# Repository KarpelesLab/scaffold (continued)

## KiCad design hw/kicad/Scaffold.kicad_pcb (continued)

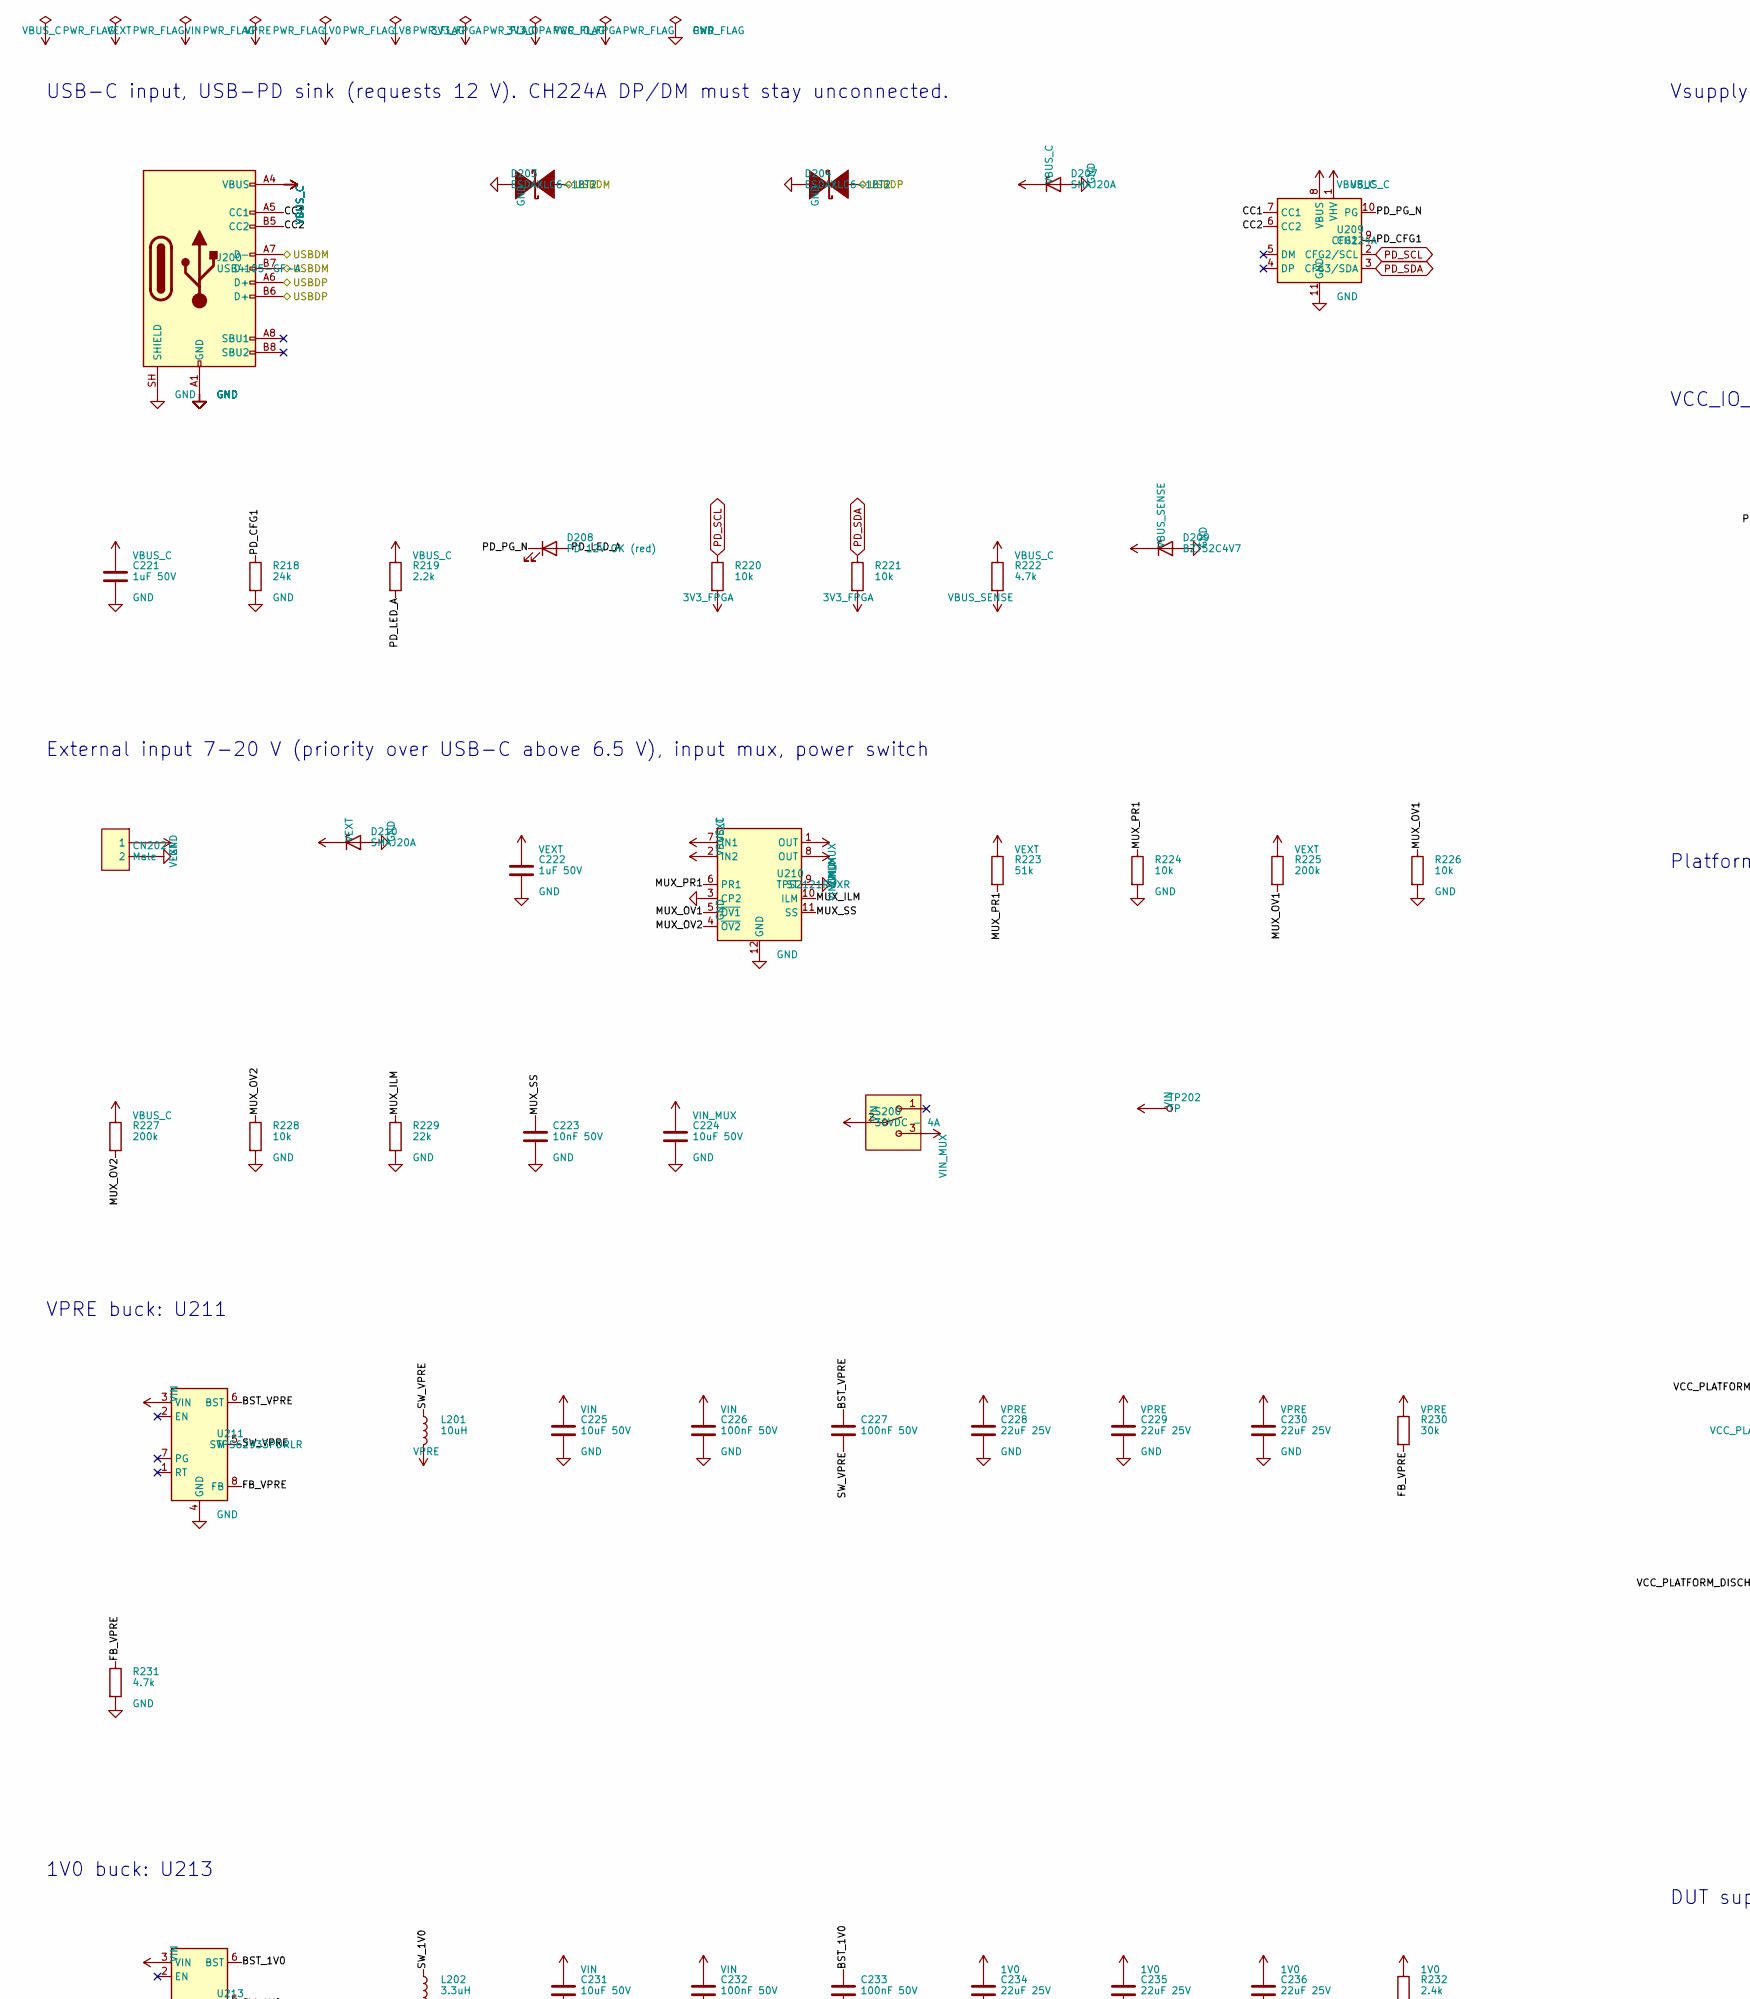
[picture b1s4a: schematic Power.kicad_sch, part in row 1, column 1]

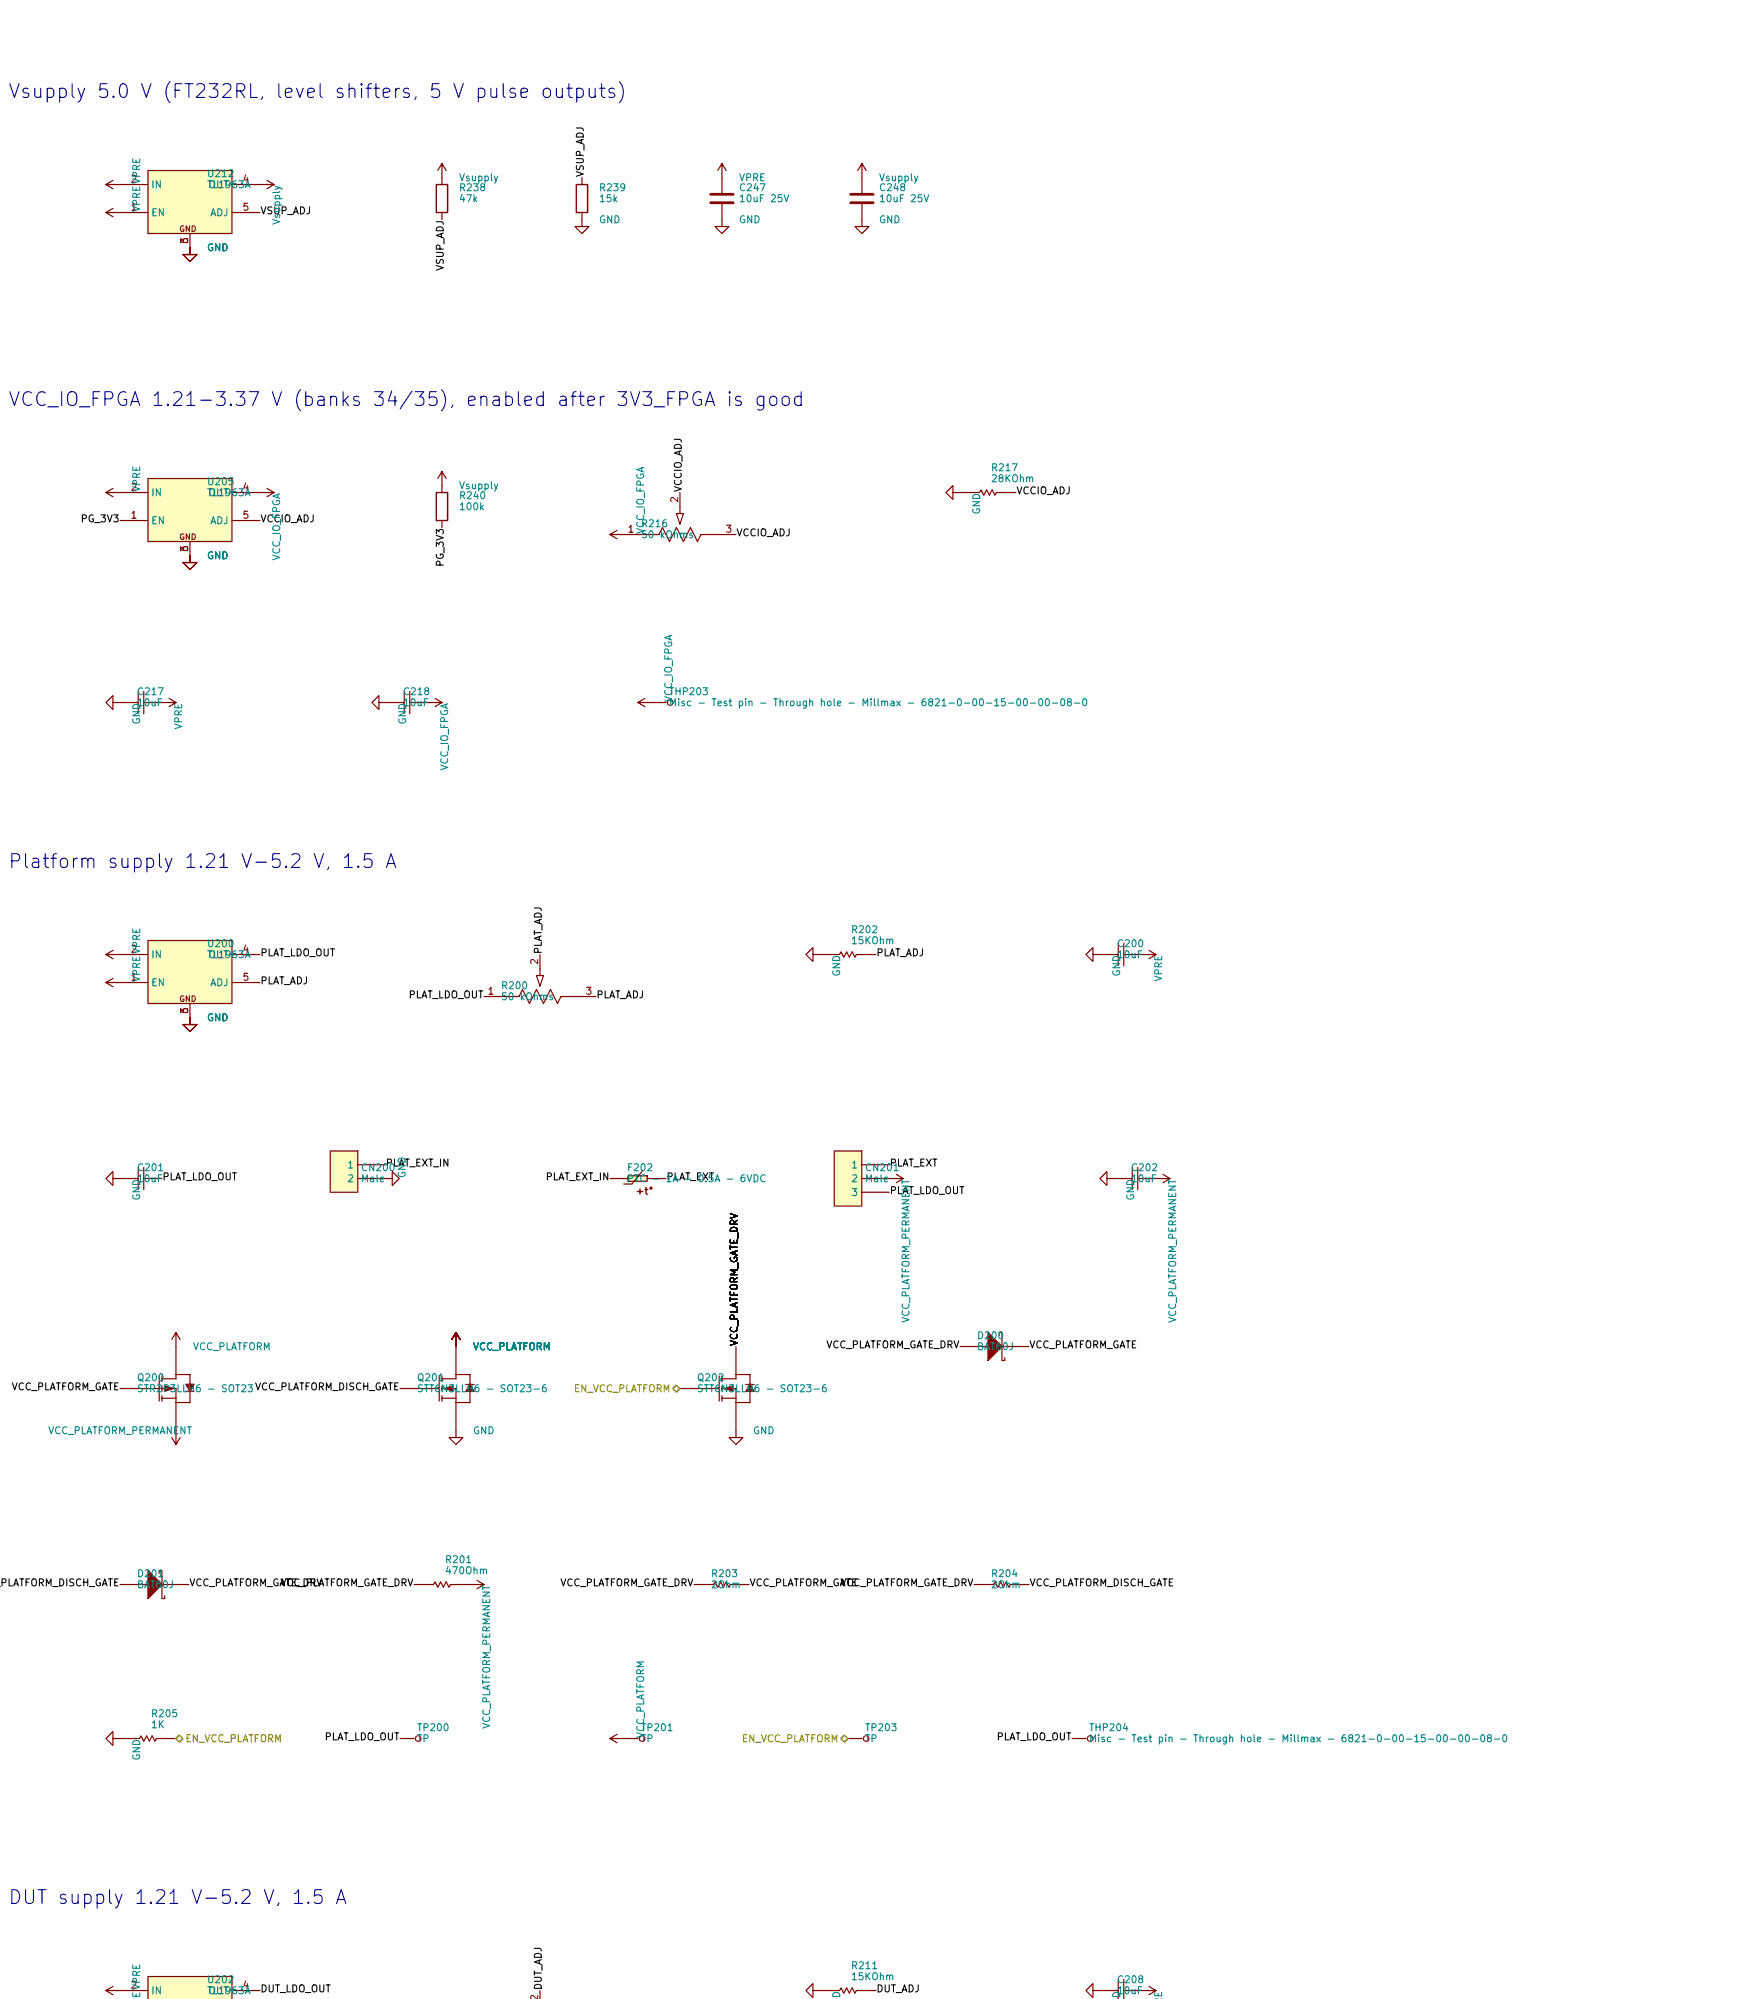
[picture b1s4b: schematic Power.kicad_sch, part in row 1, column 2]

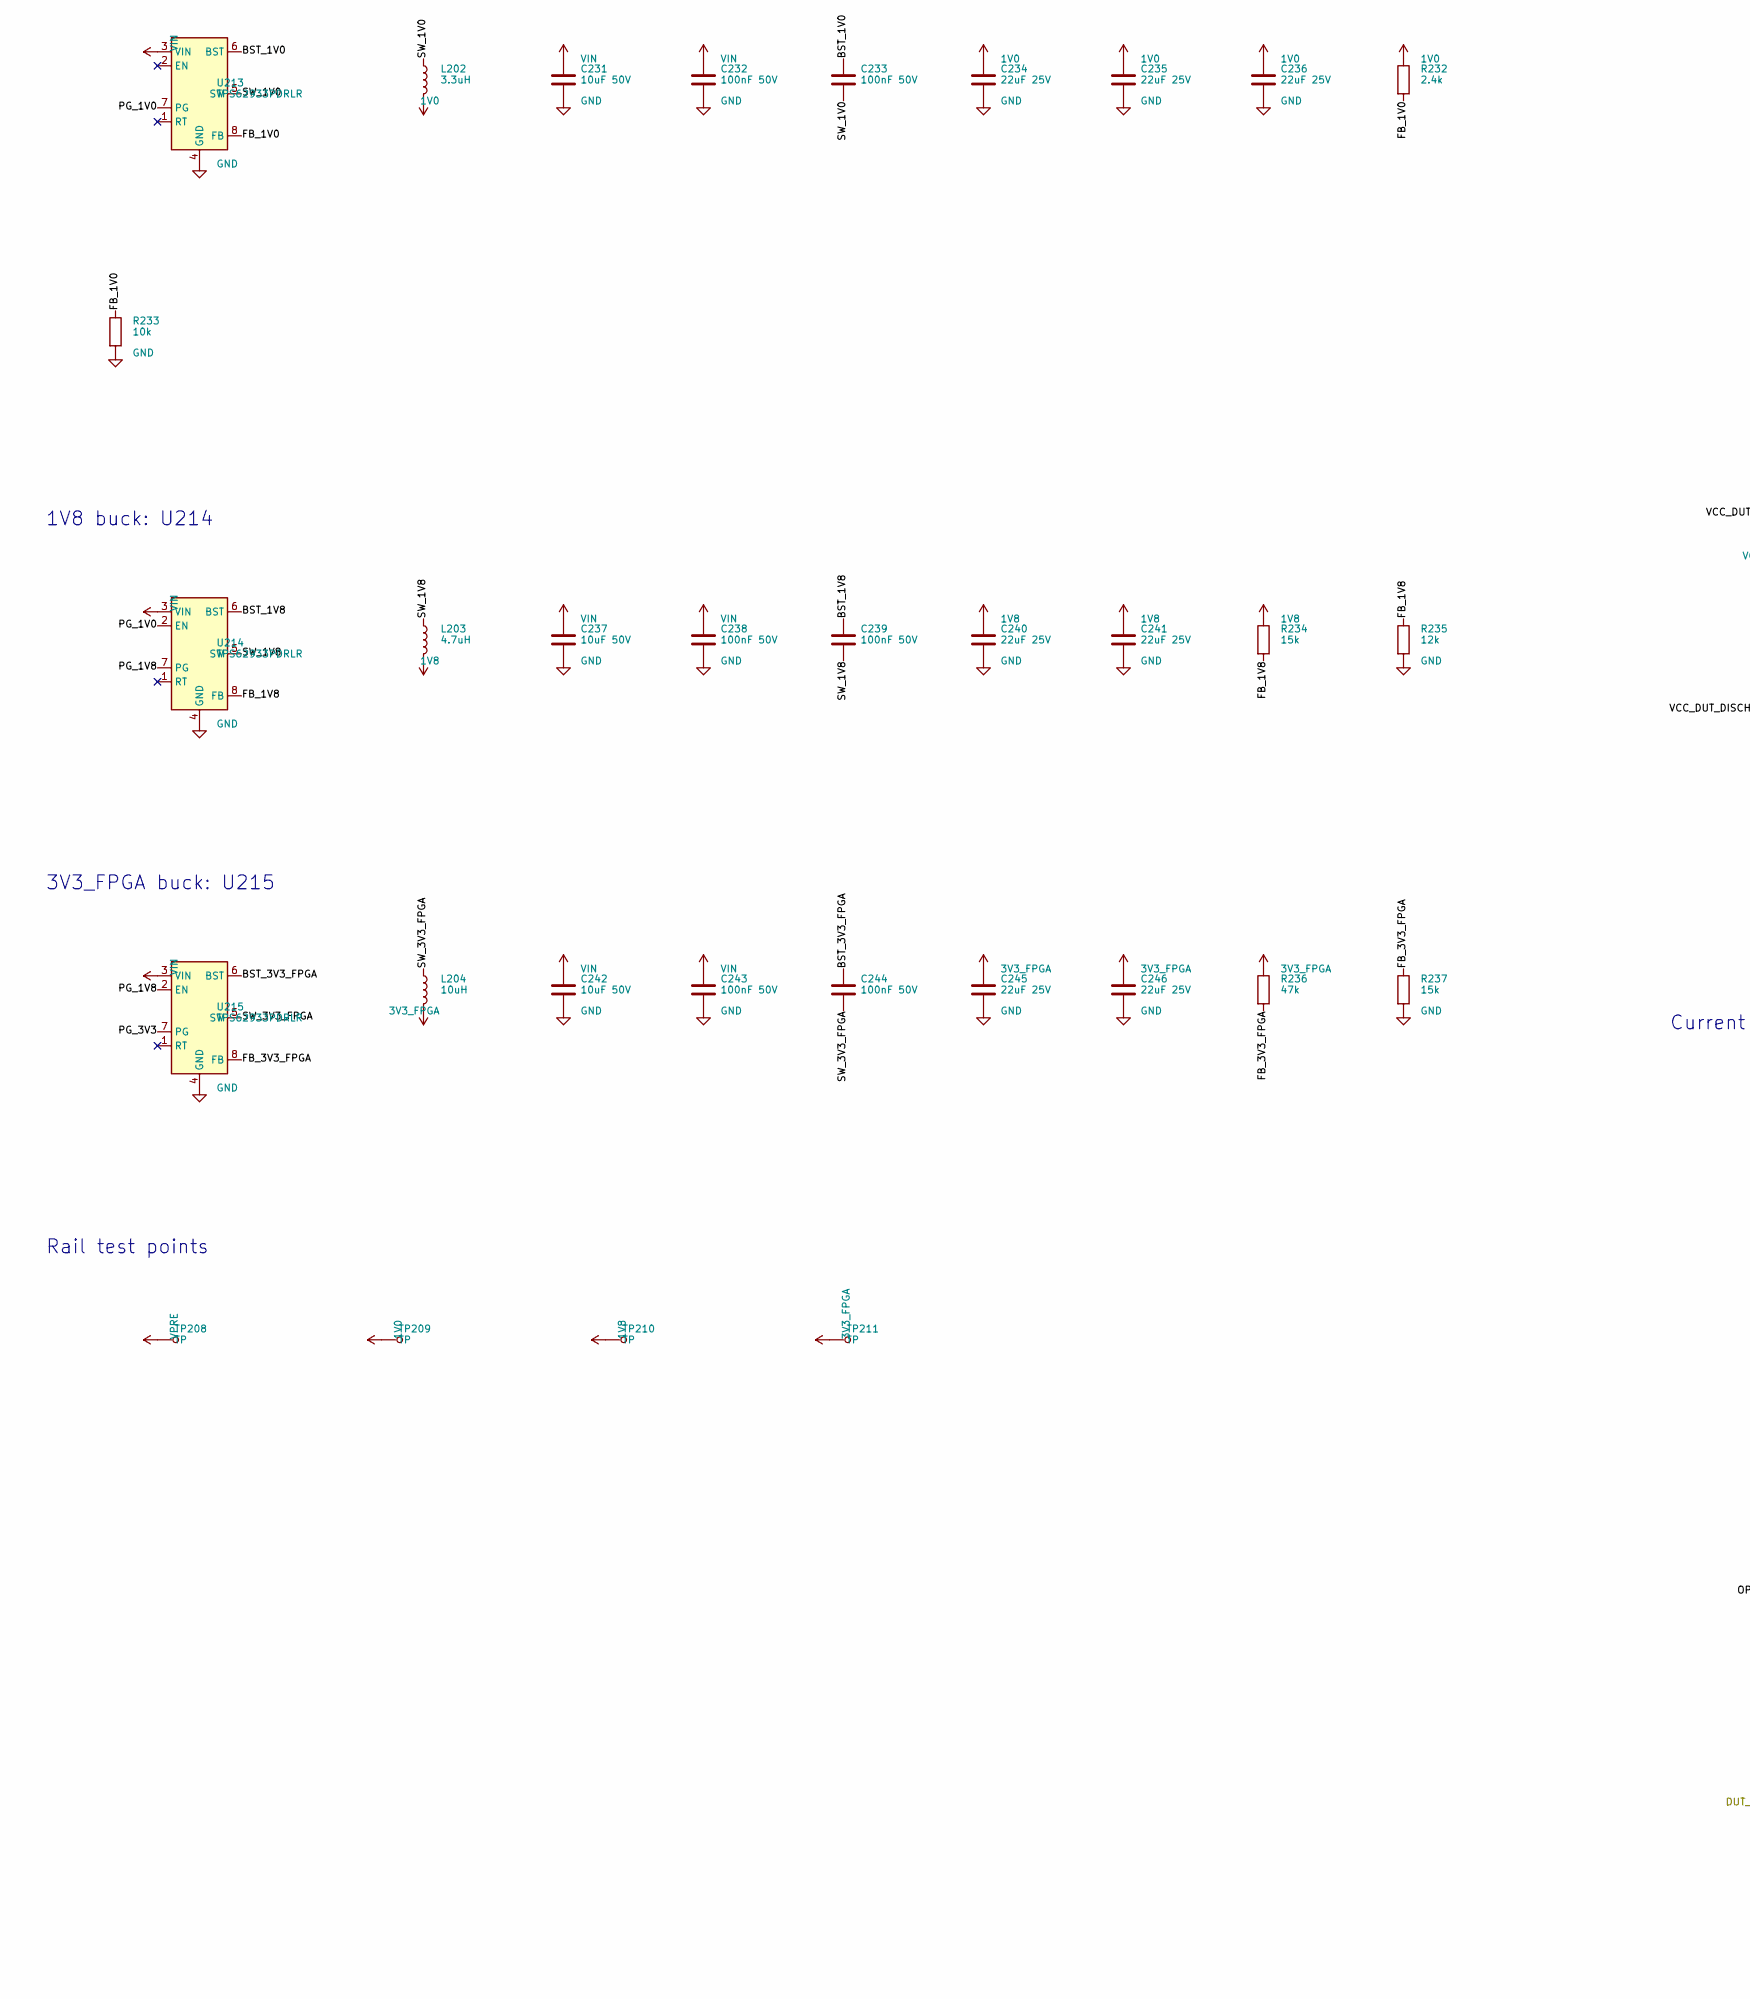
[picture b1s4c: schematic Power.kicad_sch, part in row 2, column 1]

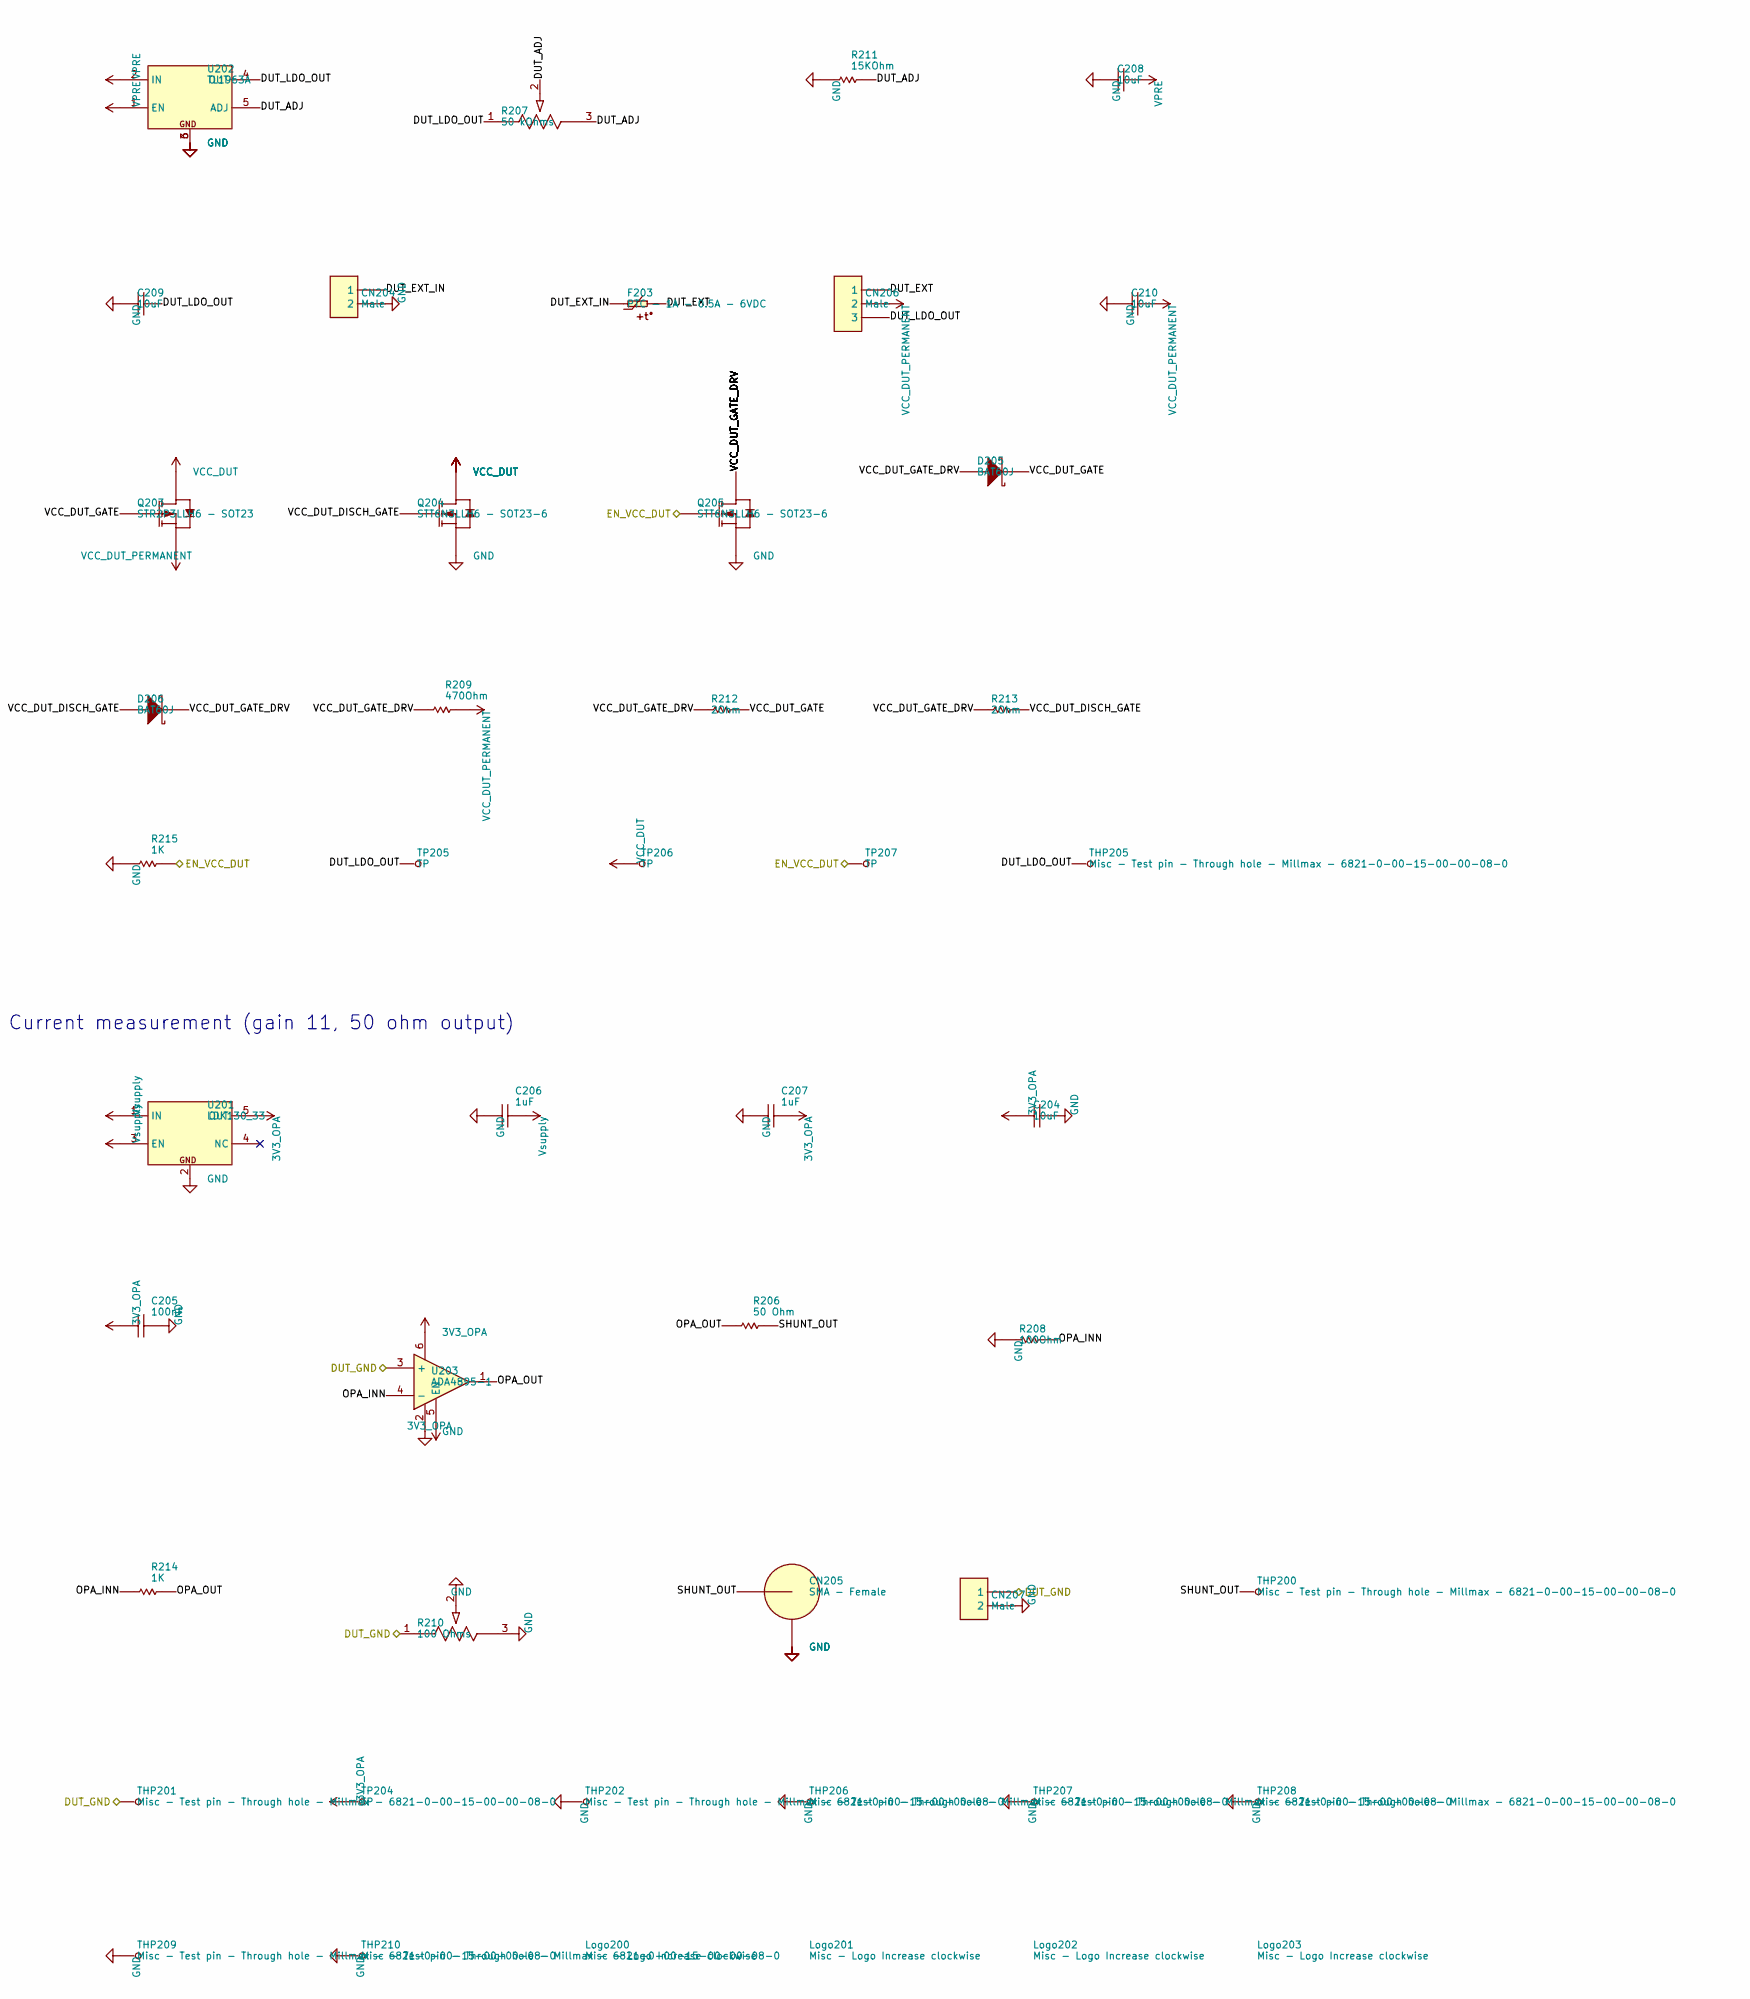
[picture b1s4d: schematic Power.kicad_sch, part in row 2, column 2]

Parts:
C200, C201, C202, C204, C208, C209, C210, C217, C218: 10uF; CAP0603; TOLERANCE 20%; MANUFACTURER PN GRM188R61C106MA73D
C205: 100nF; CAP0603; TOLERANCE 10%; MANUFACTURER1 PN CC0603KRX7R7BB104
C206, C207: 1uF; CAP0603; TOLERANCE 10%; MANUFACTURER PN C0603C105K4RACTU
C221, C222: 1uF 50V; C_0603_1608Metric; LCSC C15849
C223: 10nF 50V; C_0603_1608Metric; LCSC C57112
C224, C225, C231, C237, C242: 10uF 50V; C_1206_3216Metric; LCSC C13585
C226, C227, C232, C233, C238, C239, C243, C244: 100nF 50V; C_0603_1608Metric; LCSC C14663
C228, C229, C230, C234, C235, C236, C240, C241, C245, C246: 22uF 25V; C_0805_2012Metric; LCSC C45783
C247, C248: 10uF 25V; C_0805_2012Metric; LCSC C15850
CN200, CN202, CN204: Male; WURTH_691213710002; MANUFACTURER PN 691213710002
CN201, CN206: Male; MOLEX_90120-0123; MANUFACTURER PN 90120-0123
CN205: SMA - Female; SAMTEC_SMA-J-P-X-ST-EM3; MANUFACTURER PN SMA–J–P–H–ST–EM3
CN207: Male; MOLEX_90120-0122; MANUFACTURER PN 90120-0122
D200, D201, D205, D206: BAT60J; SOD323_A; MANUFACTURER PN BAT60J
D203, D204: ESDAXLC6-1BT2; SOD882; MANUFACTURER PN ESDAXLC6-1BT2
D207, D210: SMAJ20A; D_SMA; LCSC C115250
D208: PD 12V OK (red); LED_0603_1608Metric; LCSC C2286
D209: BZT52C4V7; D_SOD-123; LCSC C2116
F202, F203: PTC - 1A - 0.5A - 6VDC; FUSE_0805; VOLTAGE 6V; MANUFACTURER PN 0ZCK0050FF2E
J200: USB4105-GF-A; USB_C_Receptacle_GCT_USB4105-xx-A_16P_TopMnt_Horizontal; MANUFACTURER PN USB4105-GF-A; LCSC C3020560
L201: 10uH; L_CJiang_FXL1040; LCSC C475915
L202: 3.3uH; L_Changjiang_FNR6045S; LCSC C168063
L203: 4.7uH; L_Changjiang_FNR6045S; LCSC C168067
L204: 10uH; L_Changjiang_FNR6045S; LCSC C168076
Logo200, Logo201, Logo202, Logo203: Misc - Logo Increase clockwise; LOGO_CLOCKWISE_INCREASE
Q200, Q203: STR2P3LLH6 - SOT23; SOT23; MANUFACTURER PN STR2P3LLH6
Q201, Q202, Q204, Q205: STT6N3LLH6 - SOT23-6; SOT95P280X145-6N; MANUFACTURER PN STT6N3LLH6
R200, R207, R216: 50 kOhms; POT_3296W; TOLERANCE 10%; MANUFACTURER PN 3296W-1-503RLF
R201, R209: 470Ohm; RES0603; TOLERANCE 1%; MANUFACTURER PN RC0603FR-07470RP
R202, R211: 15KOhm; RES0603; TOLERANCE 1%; MANUFACTURER PN RC0603FR-1015KL
R203, R204, R212, R213: 2Ohm; RES0603; TOLERANCE 1%; MANUFACTURER PN CRCW06032R00FKEA
R205, R214, R215: 1K; RES0603; TOLERANCE 1%; MANUFACTURER PN RC0603FR-071KL
R206: 50 Ohm; RES0603; TOLERANCE 1%; MANUFACTURER PN CRCW060350R0FKEA
R208: 100Ohm; RES0603; TOLERANCE 1%; MANUFACTURER PN CRCW0603100RFKEA
R210: 100 Ohms; POT_3296W; TOLERANCE 10%; MANUFACTURER PN 3296W-1-101LF
R217: 28KOhm; RES0603; TOLERANCE 1%; MANUFACTURER PN AC0603FR-0728KL
R218: 24k; R_0603_1608Metric; LCSC C23352
R219: 2.2k; R_0603_1608Metric; LCSC C4190
R220, R221, R224, R226, R228, R233: 10k; R_0603_1608Metric; LCSC C25804
R222, R231: 4.7k; R_0603_1608Metric; LCSC C23162
R223: 51k; R_0603_1608Metric; LCSC C23196
R225, R227: 200k; R_0603_1608Metric; LCSC C25811
R229: 22k; R_0603_1608Metric; LCSC C31850
R230: 30k; R_0603_1608Metric; LCSC C22984
R232: 2.4k; R_0603_1608Metric; LCSC C22940
R234, R237, R239: 15k; R_0603_1608Metric; LCSC C22809
R235: 12k; R_0603_1608Metric; LCSC C22790
R236, R238: 47k; R_0603_1608Metric; LCSC C25819
R240: 100k; R_0603_1608Metric; LCSC C25803
S200: 30VDC - 4A; SWITCH_25136NAH; MANUFACTURER PN 25136NAH
THP200, THP201, THP202, THP203, THP204, THP205, THP206, THP207, THP208, THP209, THP210: Misc - Test pin - Through hole - Millmax - 6821-0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; MILLMAX_6821-0-00-15-00-00-08-0; MANUFACTURER PN 6821-0-00-15-00-00-08-0
TP200, TP201, TP202, TP203, TP204, TP205, TP206, TP207, TP208, TP209, TP210, TP211: TP; TP_001
U200, U202, U205, U212: TL1963A; SOT223-6; TOLERANCE 70mV; MANUFACTURER PN TL1963ADCQR; LCSC C86720
U201: LDK130_33; SOT95P280X145-5L30; TOLERANCE 3%; MANUFACTURER PN LDK130M33R
U203: ADA4895-1; SOT95P280X145-6N; MANUFACTURER PN ADA4895-1ARJZ-R
U209: CH224A; SSOP-10-1EP_3.9x4.9mm_P1mm_EP2.1x3.3mm; LCSC C42459160
U210: TPS2121RUXR; Texas_VQFN-HR-12_2x2.5mm_P0.5mm; LCSC C485916
U211, U213, U214, U215: TPS62933PDRLR; SOT-583-8; LCSC C5219254

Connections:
1V0: C234.1, C235.1, C236.1, L202.2, R232.1, TP209.1; also elsewhere on the board
1V8: C240.1, C241.1, L203.2, R234.1, TP210.1; also elsewhere on the board
3V3_FPGA: C245.1, C246.1, L204.2, R220.2, R221.2, R236.1, TP211.1; also elsewhere on the board
3V3_OPA: C204.1, C205.1, C207.2, TP204.1, U201.5 (OUT), U203.5 (EN), U203.6 (VS+)
/USBDM: D203.C (K), J200.A7 (D-), J200.B7 (D-); also elsewhere on the board
/USBDP: D204.C (K), J200.A6 (D+), J200.B6 (D+); also elsewhere on the board
/U_DUT_Platform/DUT_GND: CN207.1, R210.1, THP201.1, U203.3 (+); also elsewhere on the board
/U_FPGA/EN_VCC_DUT: Q205.3 (G), R215.2, TP207.1; also elsewhere on the board
/U_FPGA/EN_VCC_PLATFORM: Q202.3 (G), R205.2, TP203.1; also elsewhere on the board
/U_Power/BST_1V0: C233.1, U213.6 (BST)
/U_Power/BST_1V8: C239.1, U214.6 (BST)
/U_Power/BST_3V3_FPGA: C244.1, U215.6 (BST)
/U_Power/BST_VPRE: C227.1, U211.6 (BST)
/U_Power/CC1: J200.A5 (CC1), U209.7 (CC1)
/U_Power/CC2: J200.B5 (CC2), U209.6 (CC2)
/U_Power/DUT_ADJ: R207.2, R207.3, R211.2, U202.5 (ADJ)
/U_Power/DUT_EXT: CN206.1, F203.2
/U_Power/DUT_EXT_IN: CN204.1, F203.1
/U_Power/DUT_LDO_OUT: C209.2, CN206.3, R207.1, THP205.1, TP205.1, U202.4 (OUT)
/U_Power/FB_1V0: R232.2, R233.1, U213.8 (FB)
/U_Power/FB_1V8: R234.2, R235.1, U214.8 (FB)
/U_Power/FB_3V3_FPGA: R236.2, R237.1, U215.8 (FB)
/U_Power/FB_VPRE: R230.2, R231.1, U211.8 (FB)
/U_Power/MUX_ILM: R229.1, U210.10 (ILM)
/U_Power/MUX_OV1: R225.2, R226.1, U210.5 (~OV1)
/U_Power/MUX_OV2: R227.2, R228.1, U210.4 (~OV2)
/U_Power/MUX_PR1: R223.2, R224.1, U210.6 (PR1)
/U_Power/MUX_SS: C223.1, U210.11 (SS)
/U_Power/OPA_INN: R208.2, R214.1, U203.4 (-)
/U_Power/OPA_OUT: R206.1, R214.2, U203.1 (Out)
/U_Power/PD_CFG1: R218.1, U209.9 (CFG1)
/U_Power/PD_LED_A: D208.2 (A), R219.2
/U_Power/PD_PG_N: D208.1 (K), U209.10 (PG)
/U_Power/PG_1V0: U213.7 (PG), U214.2 (EN)
/U_Power/PG_1V8: U214.7 (PG), U215.2 (EN)
/U_Power/PG_3V3: R240.2, U205.1 (EN), U215.7 (PG)
/U_Power/PLAT_ADJ: R200.2, R200.3, R202.2, U200.5 (ADJ)
/U_Power/PLAT_EXT: CN201.1, F202.2
/U_Power/PLAT_EXT_IN: CN200.1, F202.1
/U_Power/PLAT_LDO_OUT: C201.2, CN201.3, R200.1, THP204.1, TP200.1, U200.4 (OUT)
/U_Power/SHUNT_OUT: CN205.1, R206.2, THP200.1
/U_Power/SW_1V0: C233.2, L202.1, U213.5 (SW)
/U_Power/SW_1V8: C239.2, L203.1, U214.5 (SW)
/U_Power/SW_3V3_FPGA: C244.2, L204.1, U215.5 (SW)
/U_Power/SW_VPRE: C227.2, L201.1, U211.5 (SW)
/U_Power/VCCIO_ADJ: R216.2, R216.3, R217.2, U205.5 (ADJ)
/U_Power/VCC_DUT_DISCH_GATE: D206.1 (A), Q204.3 (G), R213.2
/U_Power/VCC_DUT_GATE: D205.2 (K), Q203.1 (G), R212.2
/U_Power/VCC_DUT_GATE_DRV: D205.1 (A), D206.2 (K), Q205.1 (D), Q205.2 (D), Q205.5 (D), Q205.6 (D), R209.1, R212.1, R213.1
/U_Power/VCC_PLATFORM_DISCH_GATE: D201.1 (A), Q201.3 (G), R204.2
/U_Power/VCC_PLATFORM_GATE: D200.2 (K), Q200.1 (G), R203.2
/U_Power/VCC_PLATFORM_GATE_DRV: D200.1 (A), D201.2 (K), Q202.1 (D), Q202.2 (D), Q202.5 (D), Q202.6 (D), R201.1, R203.1, R204.1
/U_Power/VSUP_ADJ: R238.2, R239.1, U212.5 (ADJ)
GND: C200.1, C201.1, C202.1, C204.2, C205.2, C206.1, C207.1, C208.1, C209.1, C210.1, C217.1, C218.1, C221.2, C222.2, C223.2, C224.2, C225.2, C226.2, C228.2, C229.2, C230.2, C231.2, C232.2, C234.2, C235.2, C236.2, C237.2, C238.2, C240.2, C241.2, C242.2, C243.2, C245.2, C246.2, C247.2, C248.2, CN200.2, CN202.2, CN204.2, CN205.2, CN205.3, CN207.2, D203.A, D204.A, D207.2 (A), D209.2 (A), D210.2 (A), J200.A1 (GND), J200.A12 (GND), J200.B1 (GND), J200.B12 (GND), J200.SH (SHIELD), Q201.4 (S), Q202.4 (S), Q204.4 (S), Q205.4 (S), R202.1, R205.1, R208.1, R210.2, R210.3, R211.1, R215.1, R217.1, R218.2, R224.2, R226.2, R228.2, R229.2, R231.2, R233.2, R235.2, R237.2, R239.2, THP202.1, THP206.1, THP207.1, THP208.1, THP209.1, THP210.1, U200.3 (GND), U200.6 (GND), U201.2 (GND), U202.3 (GND), U202.6 (GND), U203.2 (GND), U205.3 (GND), U205.6 (GND), U209.11 (GND), U210.3 (CP2), U210.9 (ST), U210.12 (GND), U211.4 (GND), U212.3 (GND), U212.6 (GND), U213.4 (GND), U214.4 (GND), U215.4 (GND); also elsewhere on the board
PD_SCL: R220.1, U209.2 (CFG2/SCL); also elsewhere on the board
PD_SDA: R221.1, U209.3 (CFG3/SDA); also elsewhere on the board
VBUS_C: C221.1, D207.1 (K), J200.A4 (VBUS), J200.A9 (VBUS), J200.B4 (VBUS), J200.B9 (VBUS), R219.1, R222.1, R227.1, U209.1 (VHV), U209.8 (VBUS), U210.2 (IN2)
VBUS_SENSE: D209.1 (K), R222.2; also elsewhere on the board
VCC_DUT: Q203.3 (D), Q204.1 (D), Q204.2 (D), Q204.5 (D), Q204.6 (D), TP206.1; also elsewhere on the board
VCC_DUT_PERMANENT: C210.2, CN206.2, Q203.2 (S), R209.2; also elsewhere on the board
VCC_IO_FPGA: C218.2, R216.1, THP203.1, U205.4 (OUT); also elsewhere on the board
VCC_PLATFORM: Q200.3 (D), Q201.1 (D), Q201.2 (D), Q201.5 (D), Q201.6 (D), TP201.1; also elsewhere on the board
VCC_PLATFORM_PERMANENT: C202.2, CN201.2, Q200.2 (S), R201.2; also elsewhere on the board
VEXT: C222.1, CN202.1, D210.1 (K), R223.1, R225.1, U210.7 (IN1)
VIN: C225.1, C226.1, C231.1, C232.1, C237.1, C238.1, C242.1, C243.1, S200.2, TP202.1, U211.3 (VIN), U213.3 (VIN), U214.3 (VIN), U215.3 (VIN)
VIN_MUX: C224.1, S200.3, U210.1 (OUT), U210.8 (OUT)
VPRE: C200.2, C208.2, C217.2, C228.1, C229.1, C230.1, C247.1, L201.2, R230.1, TP208.1, U200.1 (EN), U200.2 (IN), U202.1 (EN), U202.2 (IN), U205.2 (IN), U212.1 (EN), U212.2 (IN)
Vsupply: C206.2, C248.1, R238.1, R240.1, U201.1 (IN), U201.3 (EN), U212.4 (OUT); also elsewhere on the board

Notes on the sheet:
USB-C input, USB-PD sink (requests 12 V). CH224A DP/DM must stay unconnected.
External input 7-20 V (priority over USB-C above 6.5 V), input mux, power switch
VPRE buck: U211
1V0 buck: U213
1V8 buck: U214
3V3_FPGA buck: U215
Rail test points
Vsupply 5.0 V (FT232RL, level shifters, 5 V pulse outputs)
VCC_IO_FPGA 1.21-3.37 V (banks 34/35), enabled after 3V3_FPGA is good
Platform supply 1.21 V-5.2 V, 1.5 A
DUT supply 1.21 V-5.2 V, 1.5 A
Current measurement (gain 11, 50 ohm output)
